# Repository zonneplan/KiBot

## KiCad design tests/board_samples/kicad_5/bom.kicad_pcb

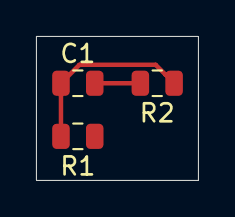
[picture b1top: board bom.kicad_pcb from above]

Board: 2 copper layers, 9.0 x 8.0 mm, 3 parts (0 on the bottom side), 2 nets.

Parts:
C1: 1uF; C_0805_2012Metric
R1: 100; R_0805_2012Metric
R2: 200; R_0805_2012Metric

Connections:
GND: C1.2, R2.2
unnamed: C1.1, R1.2, R2.1
